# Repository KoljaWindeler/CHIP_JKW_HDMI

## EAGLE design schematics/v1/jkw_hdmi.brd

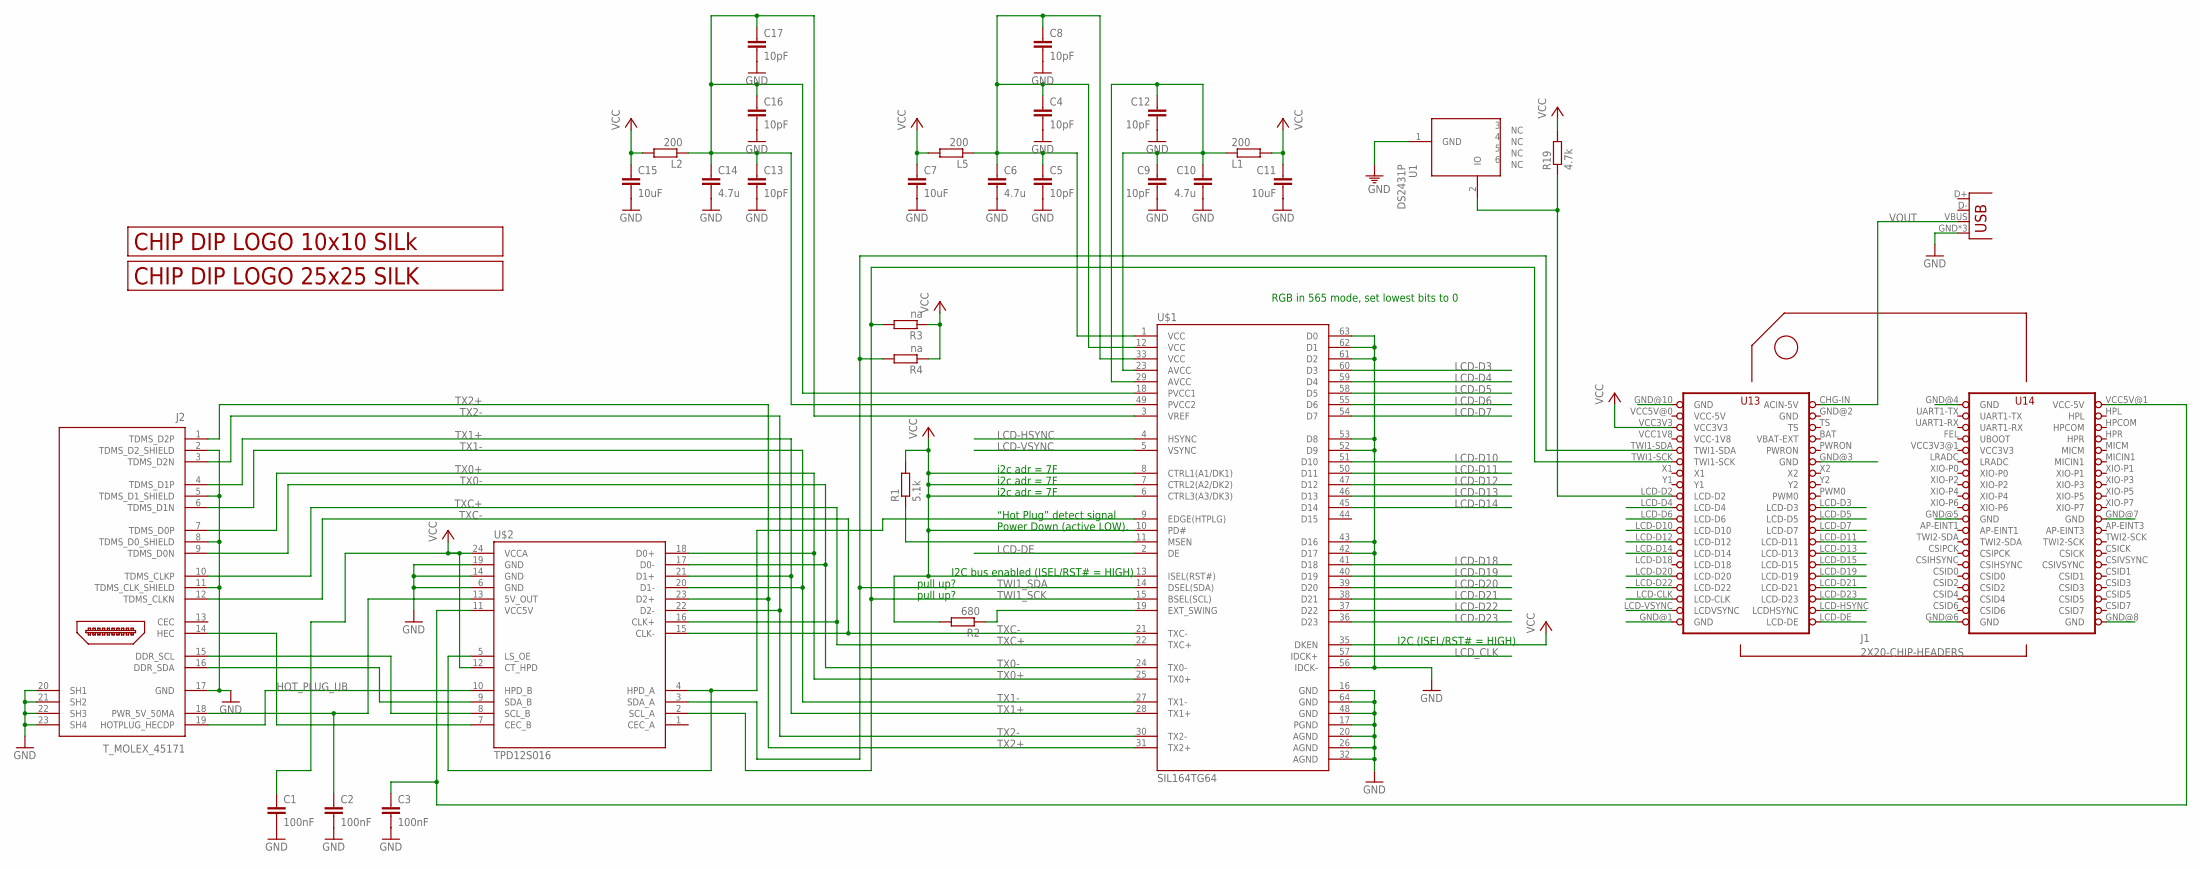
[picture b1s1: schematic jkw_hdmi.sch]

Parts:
C1, C2, C3: 100nF; C0805
C4, C5, C8, C9, C12, C13, C16, C17: 10pF; C0805
C6, C10, C14: 4.7u; C0805
C7, C11, C15: 10uF; C0805
J1: 2X20-CHIP-HEADERS; 2X20CHIP_SM
J2: T_MOLEX_45171
L1, L2, L5: 200; R0805
POWER_USB: USBUSB-MICROB-SMT-DIP; USB-MICROB-SMT-DIP
R1: 5.1k; M0805
R2: 680; M0805
R3, R4: na; M0805
R19: 4.7k; R0805
U1: DS2431P; TSOC6
U$1: SIL164TG64; TQFP64
U$2: TPD12S016; DIL24
U$3: LOGO_10X10_SILK
U$4: LOGO_25X25_SILK

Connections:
ASD: R1.1, U$1.11 (MSEN)
D15: U$1.44 (D15)
GND: C1.2, C2.2, C3.2, C4.2, C5.2, C6.2, C7.2, C8.2, C9.2, C10.2, C11.2, C12.2, C13.2, C14.2, C15.2, C16.2, C17.2, J1.GND@1 (GND), J1.GND@2 (GND), J1.GND@3 (GND), J1.GND@4 (GND), J1.GND@5 (GND), J1.GND@6 (GND), J1.GND@7 (GND), J1.GND@8 (GND), J1.GND@10 (GND), J2.2 (TDMS_D2_SHIELD), J2.5 (TDMS_D1_SHIELD), J2.8 (TDMS_D0_SHIELD), J2.11 (TDMS_CLK_SHIELD), J2.17 (GND), J2.20 (SH1), J2.21 (SH2), J2.22 (SH3), J2.23 (SH4), POWER_USB.GND, POWER_USB.MT1 (GND), POWER_USB.MT2 (GND), U1.1 (GND), U$1.16 (GND), U$1.17 (PGND), U$1.20 (AGND), U$1.26 (AGND), U$1.32 (AGND), U$1.42 (D17), U$1.43 (D16), U$1.48 (GND), U$1.52 (D9), U$1.53 (D8), U$1.56 (IDCK-), U$1.61 (D2), U$1.62 (D1), U$1.63 (D0), U$1.64 (GND), U$2.6 (GND), U$2.14 (GND), U$2.19 (GND)
HOTPLUG_DET: U$1.9 (EDGE(HTPLG)), U$2.4 (HPD_A), U$2.5 (LS_OE)
HOT_PLUG_UB: J2.19 (HOTPLUG_HECDP), U$2.10 (HPD_B)
LCD-D3: J1.LCD-D3, U$1.60 (D3)
LCD-D4: J1.LCD-D4, U$1.59 (D4)
LCD-D5: J1.LCD-D5, U$1.58 (D5)
LCD-D6: J1.LCD-D6, U$1.55 (D6)
LCD-D7: J1.LCD-D7, U$1.54 (D7)
LCD-D10: J1.LCD-D10, U$1.51 (D10)
LCD-D11: J1.LCD-D11, U$1.50 (D11)
LCD-D12: J1.LCD-D12, U$1.47 (D12)
LCD-D13: J1.LCD-D13, U$1.46 (D13)
LCD-D14: J1.LCD-D14, U$1.45 (D14)
LCD-D15: J1.LCD-D15
LCD-D18: U$1.41 (D18)
LCD-D19: J1.LCD-D19, U$1.40 (D19)
LCD-D20: J1.LCD-D20, U$1.39 (D20)
LCD-D21: J1.LCD-D21, U$1.38 (D21)
LCD-D22: J1.LCD-D22, U$1.37 (D22)
LCD-D23: J1.LCD-D23, U$1.36 (D23)
LCD-DE: J1.LCD-DE, U$1.2 (DE)
LCD-HSYNC: J1.LCD-HSYNC (LCDHSYNC), U$1.4 (HSYNC)
LCD-VSYNC: J1.LCD-VSYNC (LCDVSYNC), U$1.5 (VSYNC)
LCD_CLK: J1.LCD-CLK, U$1.57 (IDCK+)
unnamed: R2.1, U$1.19 (EXT_SWING)
unnamed: C2.1, J2.18 (PWR_5V_50MA), U$2.13 (5V_OUT)
unnamed: C4.1, C5.1, C6.1, C8.1, L5.1, U$1.1 (VCC), U$1.12 (VCC), U$1.33 (VCC)
unnamed: J1.LCD-D2, R19.1, U1.2 (IO)
unnamed: J2.15 (DDR_SCL), U$2.8 (SCL_B)
unnamed: J2.16 (DDR_SDA), U$2.9 (SDA_B)
unnamed: C9.1, C10.1, C12.1, L1.1, U$1.23 (AVCC), U$1.29 (AVCC)
unnamed: J2.14 (HEC), U$2.7 (CEC_B)
unnamed: C13.1, C14.1, C16.1, C17.1, L2.1, U$1.3 (VREF), U$1.18 (PVCC1), U$1.49 (PVCC2)
TWI1_SCK: J1.TWI1-SCK, R3.2, U$1.15 (BSEL(SCL)), U$2.2 (SCL_A)
TWI1_SDA: J1.TWI1-SDA, R4.2, U$1.14 (DSEL(SDA)), U$2.3 (SDA_A)
TX0+: J2.7 (TDMS_D0P), U$1.25 (TX0+), U$2.18 (D0+)
TX0-: J2.9 (TDMS_D0N), U$1.24 (TX0-), U$2.17 (D0-)
TX1+: J2.4 (TDMS_D1P), U$1.28 (TX1+), U$2.21 (D1+)
TX1-: J2.6 (TDMS_D1N), U$1.27 (TX1-), U$2.20 (D1-)
TX2+: J2.1 (TDMS_D2P), U$1.31 (TX2+), U$2.23 (D2+)
TX2-: J2.3 (TDMS_D2N), U$1.30 (TX2-), U$2.22 (D2-)
TXC+: J2.10 (TDMS_CLKP), U$1.22 (TXC+), U$2.16 (CLK+)
TXC-: J2.12 (TDMS_CLKN), U$1.21 (TXC-), U$2.15 (CLK-)
VCC: C1.1, C7.1, C11.1, C15.1, J1.VCC3V3, L1.2, L2.2, L5.2, R1.2, R2.2, R3.1, R4.1, R19.2, U$1.6 (CTRL3(A3/DK3)), U$1.7 (CTRL2(A2/DK2)), U$1.8 (CTRL1(A1/DK1)), U$1.10 (PD#), U$1.13 (ISEL(RST#)), U$1.35 (DKEN), U$2.12 (CT_HPD), U$2.24 (VCCA)
VCC3V3: J1.VCC3V3@1 (VCC3V3)
VCC-1V8: J1.VCC1V8 (VCC-1V8)
VCC-5V: J1.VCC5V@0 (VCC-5V)
VCC_5V_DCC: C3.1, J1.VCC5V@1 (VCC-5V), U$2.11 (VCC5V)
VOUT: J1.CHG-IN (ACIN-5V), POWER_USB.VBUS

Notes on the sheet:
I2C bus enabled (ISEL/RST# = HIGH)
RGB in 565 mode, set lowest bits to 0
pull up?
I2C (ISEL/RST# = HIGH)
“Hot Plug” detect signal
Power Down (active LOW).
i2c adr = 7F

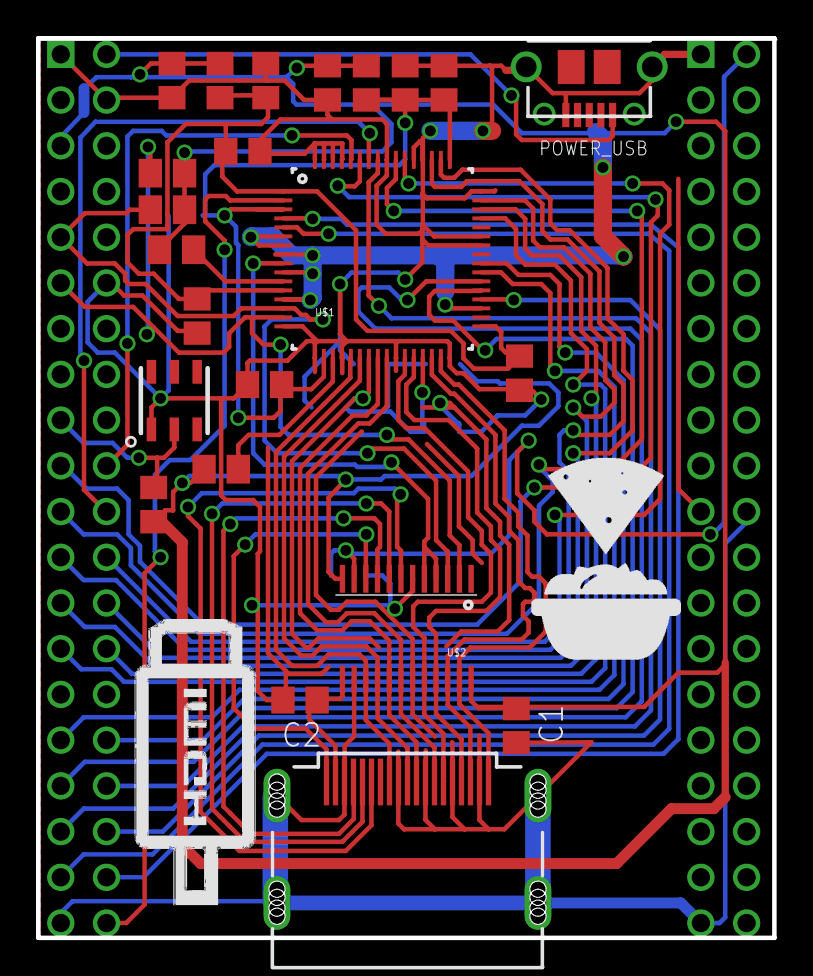
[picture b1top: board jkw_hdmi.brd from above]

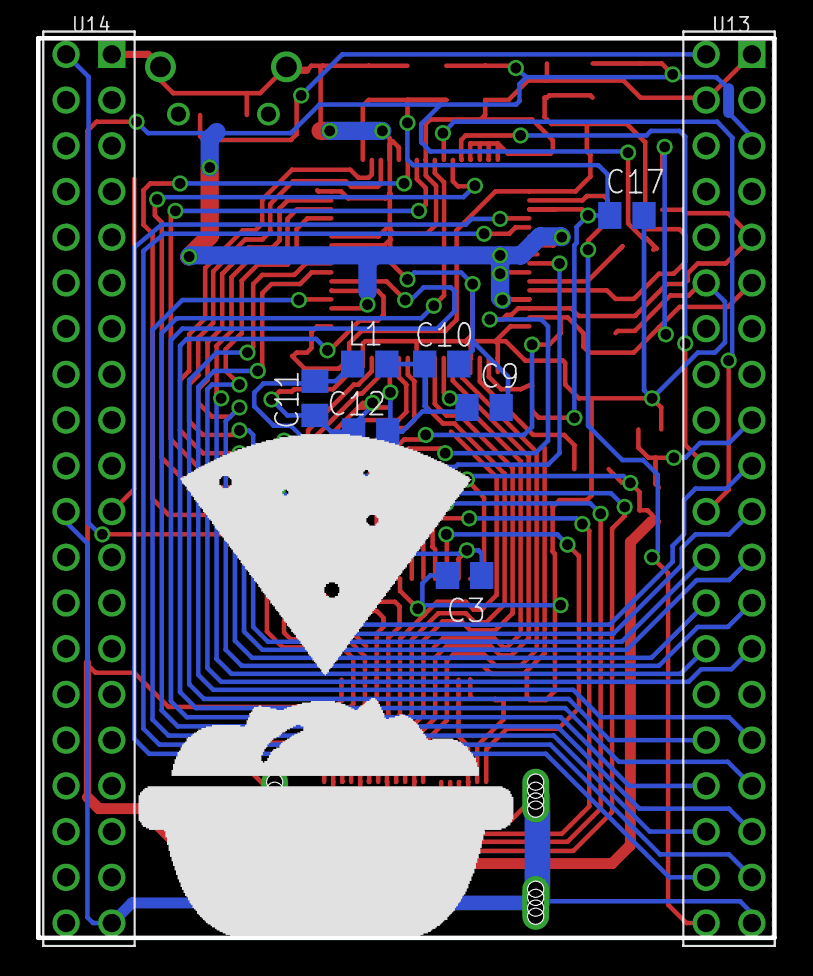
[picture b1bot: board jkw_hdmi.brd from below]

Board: 2 copper layers, 40.9 x 50.0 mm, 33 parts (8 on the bottom side), 45 nets.

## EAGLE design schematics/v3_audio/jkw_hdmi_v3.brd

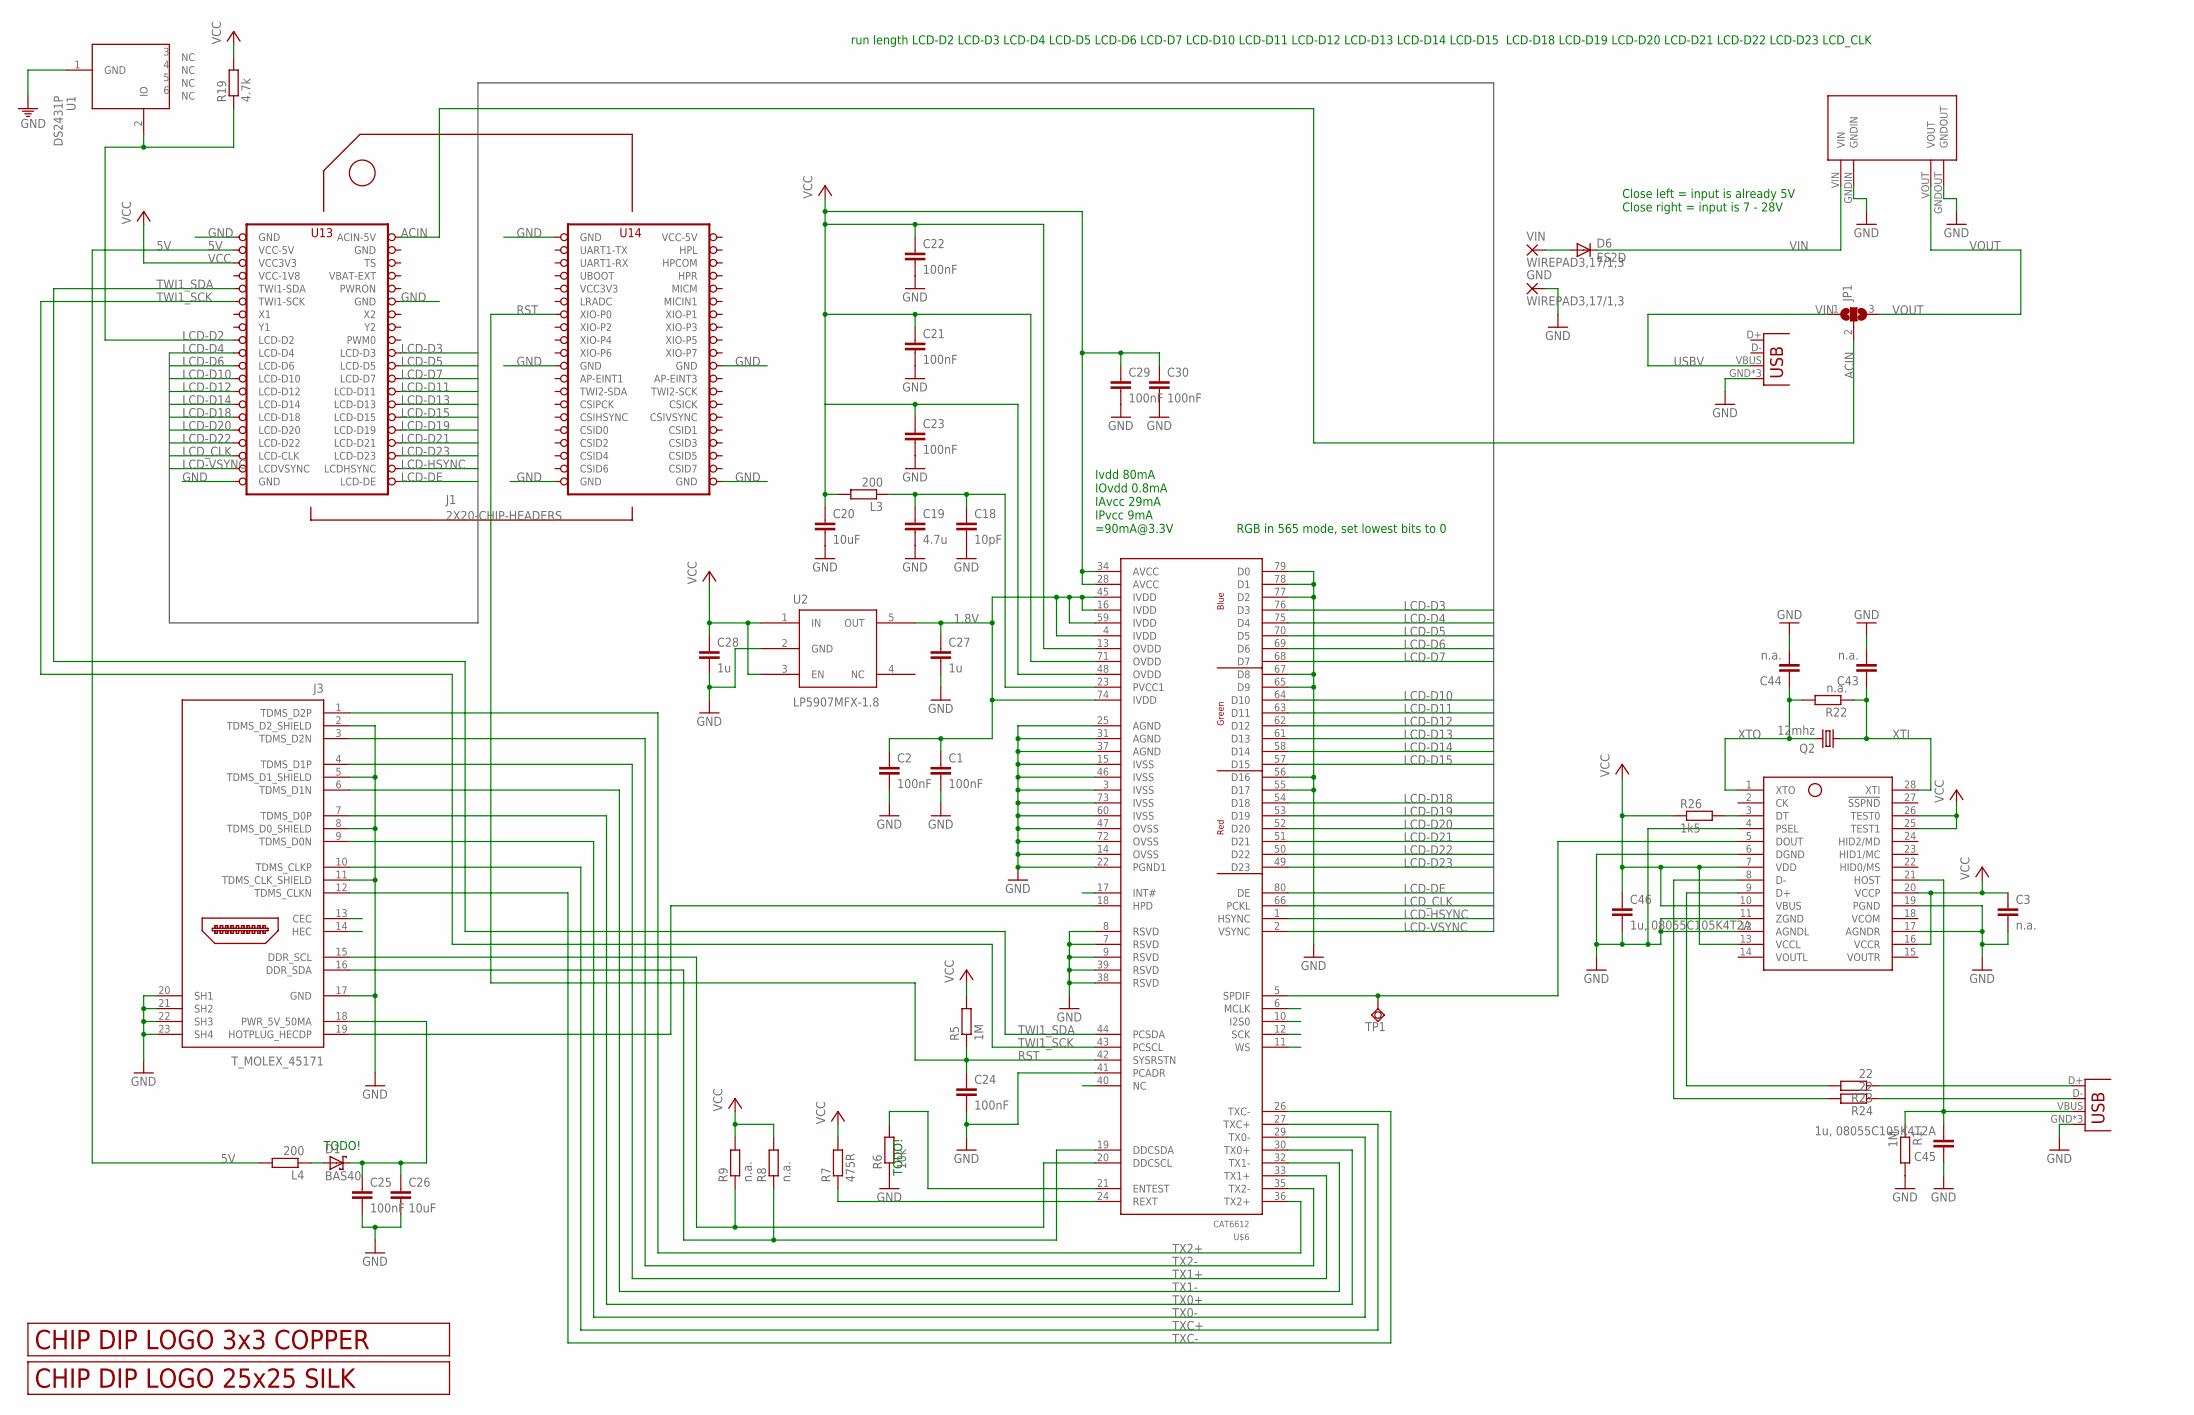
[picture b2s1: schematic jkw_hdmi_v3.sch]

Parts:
AUDIO_USB: USBUSB-MICROB-SMT-DIP; USB-MICROB-SMT-DIP
C1, C2, C21, C22, C23, C24, C25, C29, C30: 100nF; C0805
C3, C43, C44: n.a.; C0805
C18: 10pF; C0805
C19: 4.7u; C0805
C20, C26: 10uF; C0805
C27, C28: 1u; C0805
C45, C46: 1u, 08055C105K4T2A; C0805
D1: BAS40; SOT23
D6: ES2D; SMB
GND: WIREPAD3,17/1,3; 3,17/1,3
J1: 2X20-CHIP-HEADERS; 2X20CHIP_SM
J3: T_MOLEX_45171
JP1: SJ2W; SJ_2
L3, L4: 200; R0805
POWER_USB: USBUSB-MICROB-SMT-DIP; USB-MICROB-SMT-DIP
Q2: 12mhz; HC49UP
R1: 1M; M0805
R5: 1M; R0805
R6: 10k; R0805
R7: 475R; R0805
R8, R9: n.a.; R0805
R19: 4.7k; R0805
R22: n.a.; M0805
R23, R24: 22; M0805
R26: 1k5; M0805
TP1: TPSQTP12SQ; TP12SQ
U1: DS2431P; TSOC6
U2: LP5907MFX-1.8; SOT23-5
U$1: LOGO_25X25_SILK
U$4: LOGO_3X3_COPPER
U$5: PCM2704; SSOT28
U$6: CAT6612; LQFP-80
U$9: MP1584EN_FRAMELESS
VIN: WIREPAD3,17/1,3; 3,17/1,3

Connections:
1.8V: C1.1, C2.1, C27.1, U2.5 (OUT), U$6.4 (IVDD), U$6.16 (IVDD), U$6.45 (IVDD), U$6.59 (IVDD), U$6.74 (IVDD)
5V: J1.VCC5V@0 (VCC-5V), L4.2
ACIN: J1.CHG-IN (ACIN-5V), JP1.2
GND: AUDIO_USB.GND, AUDIO_USB.MT1 (GND), AUDIO_USB.MT2 (GND), C1.2, C2.2, C3.2, C18.2, C19.2, C20.2, C21.2, C22.2, C23.2, C24.2, C25.2, C26.2, C27.2, C28.2, C29.2, C30.2, C43.2, C44.2, C45.1, C46.2, GND.1, J1.GND@1 (GND), J1.GND@2 (GND), J1.GND@3 (GND), J1.GND@4 (GND), J1.GND@5 (GND), J1.GND@6 (GND), J1.GND@7 (GND), J1.GND@8 (GND), J1.GND@10 (GND), J3.2 (TDMS_D2_SHIELD), J3.5 (TDMS_D1_SHIELD), J3.8 (TDMS_D0_SHIELD), J3.11 (TDMS_CLK_SHIELD), J3.17 (GND), J3.20 (SH1), J3.21 (SH2), J3.22 (SH3), J3.23 (SH4), POWER_USB.GND, POWER_USB.MT1 (GND), POWER_USB.MT2 (GND), R1.2, R6.1, U1.1 (GND), U2.2 (GND), U$5.4 (PSEL), U$5.6 (DGND), U$5.11 (ZGND), U$5.12 (AGNDL), U$5.17 (AGNDR), U$5.19 (PGND), U$6.3 (IVSS), U$6.7 (RSVD), U$6.8 (RSVD), U$6.9 (RSVD), U$6.14 (OVSS), U$6.15 (IVSS), U$6.22 (PGND1), U$6.25 (AGND), U$6.31 (AGND), U$6.37 (AGND), U$6.38 (RSVD), U$6.39 (RSVD), U$6.41 (PCADR), U$6.46 (IVSS), U$6.47 (OVSS), U$6.55 (D17), U$6.56 (D16), U$6.60 (IVSS), U$6.65 (D9), U$6.67 (D8), U$6.72 (OVSS), U$6.73 (IVSS), U$6.77 (D2), U$6.78 (D1), U$6.79 (D0), U$9.GNDIN, U$9.GNDOUT
LCD-D2: J1.LCD-D2, R19.1, U1.2 (IO)
LCD-D3: J1.LCD-D3, U$6.76 (D3)
LCD-D4: J1.LCD-D4, U$6.75 (D4)
LCD-D5: J1.LCD-D5, U$6.70 (D5)
LCD-D6: J1.LCD-D6, U$6.69 (D6)
LCD-D7: J1.LCD-D7, U$6.68 (D7)
LCD-D10: J1.LCD-D10, U$6.64 (D10)
LCD-D11: J1.LCD-D11, U$6.63 (D11)
LCD-D12: J1.LCD-D12, U$6.62 (D12)
LCD-D13: J1.LCD-D13, U$6.61 (D13)
LCD-D14: J1.LCD-D14, U$6.58 (D14)
LCD-D15: J1.LCD-D15, U$6.57 (D15)
LCD-D18: J1.LCD-D18, U$6.54 (D18)
LCD-D19: J1.LCD-D19, U$6.53 (D19)
LCD-D20: J1.LCD-D20, U$6.52 (D20)
LCD-D21: J1.LCD-D21, U$6.51 (D21)
LCD-D22: J1.LCD-D22, U$6.50 (D22)
LCD-D23: J1.LCD-D23, U$6.49 (D23)
LCD-DE: J1.LCD-DE, U$6.80 (DE)
LCD-HSYNC: J1.LCD-HSYNC (LCDHSYNC), U$6.1 (HSYNC)
LCD-VSYNC: J1.LCD-VSYNC (LCDVSYNC), U$6.2 (VSYNC)
LCD_CLK: J1.LCD-CLK, U$6.66 (PCKL)
unnamed: J3.19 (HOTPLUG_HECDP), U$6.18 (HPD)
unnamed: C18.1, C19.1, L3.1, U$6.23 (PVCC1)
unnamed: J3.16 (DDR_SDA), R8.1, U$6.19 (DDCSDA)
unnamed: J3.15 (DDR_SCL), R9.1, U$6.20 (DDCSCL)
unnamed: R6.2, U$6.21 (ENTEST)
unnamed: R7.1, U$6.24 (REXT)
unnamed: TP1.TP, U$5.5 (DOUT), U$6.5 (SPDIF)
unnamed: D1.1 (A), L4.1
unnamed: C25.1, C26.1, D1.3 (C), J3.18 (PWR_5V_50MA)
unnamed: R23.2, U$5.9 (D+)
unnamed: AUDIO_USB.D+, R23.1
unnamed: R24.2, U$5.8 (D-)
unnamed: AUDIO_USB.D-, R24.1
unnamed: D6.A, VIN.1
unnamed: R26.2, U$5.3 (DT)
RST: C24.1, J1.XIO-P0, R5.1, U$6.42 (SYSRSTN)
TWI1_SCK: J1.TWI1-SCK, U$6.43 (PCSCL)
TWI1_SDA: J1.TWI1-SDA, U$6.44 (PCSDA)
TX0+: J3.7 (TDMS_D0P), U$6.30 (TX0+)
TX0-: J3.9 (TDMS_D0N), U$6.29 (TX0-)
TX1+: J3.4 (TDMS_D1P), U$6.33 (TX1+)
TX1-: J3.6 (TDMS_D1N), U$6.32 (TX1-)
TX2+: J3.1 (TDMS_D2P), U$6.36 (TX2+)
TX2-: J3.3 (TDMS_D2N), U$6.35 (TX2-)
TXC+: J3.10 (TDMS_CLKP), U$6.27 (TXC+)
TXC-: J3.12 (TDMS_CLKN), U$6.26 (TXC-)
USBV: JP1.1, POWER_USB.VBUS
VCC: C3.1, C20.1, C21.1, C22.1, C23.1, C28.1, C29.1, C30.1, C46.1, J1.VCC3V3, L3.2, R5.2, R7.2, R8.2, R9.2, R19.2, R26.1, U2.1 (IN), U2.3 (EN), U$5.7 (VDD), U$5.10 (VBUS), U$5.13 (VCCL), U$5.16 (VCCR), U$5.20 (VCCP), U$5.25 (TEST1), U$5.26 (TEST0), U$6.13 (OVDD), U$6.28 (AVCC), U$6.34 (AVCC), U$6.48 (OVDD), U$6.71 (OVDD)
VCC2: AUDIO_USB.VBUS, C45.2, R1.1, U$5.21 (HOST)
VCC3V3: J1.VCC3V3@1 (VCC3V3)
VCC-1V8: J1.VCC1V8 (VCC-1V8)
VCC-5V: J1.VCC5V@1 (VCC-5V)
VCOM: U$5.18 (VCOM)
VIN: D6.C, U$9.VIN
VOUT: JP1.3, U$9.VOUT
XTI: C43.1, Q2.1, R22.1, U$5.28 (XTI)
XTO: C44.1, Q2.2, R22.2, U$5.1 (XTO)

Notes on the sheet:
Close left = input is already 5V Close right = input is 7 - 28V
RGB in 565 mode, set lowest bits to 0
TODO!
Ivdd 80mA IOvdd 0.8mA IAvcc 29mA IPvcc 9mA =90mA@3.3V
run length LCD-D2 LCD-D3 LCD-D4 LCD-D5 LCD-D6 LCD-D7 LCD-D10 LCD-D11 LCD-D12 LCD-D13 LCD-D14 LCD-D15 LCD-D18 LCD-D19 LCD-D20 LCD-D21 LCD-D22 LCD-D23 LCD_CLK

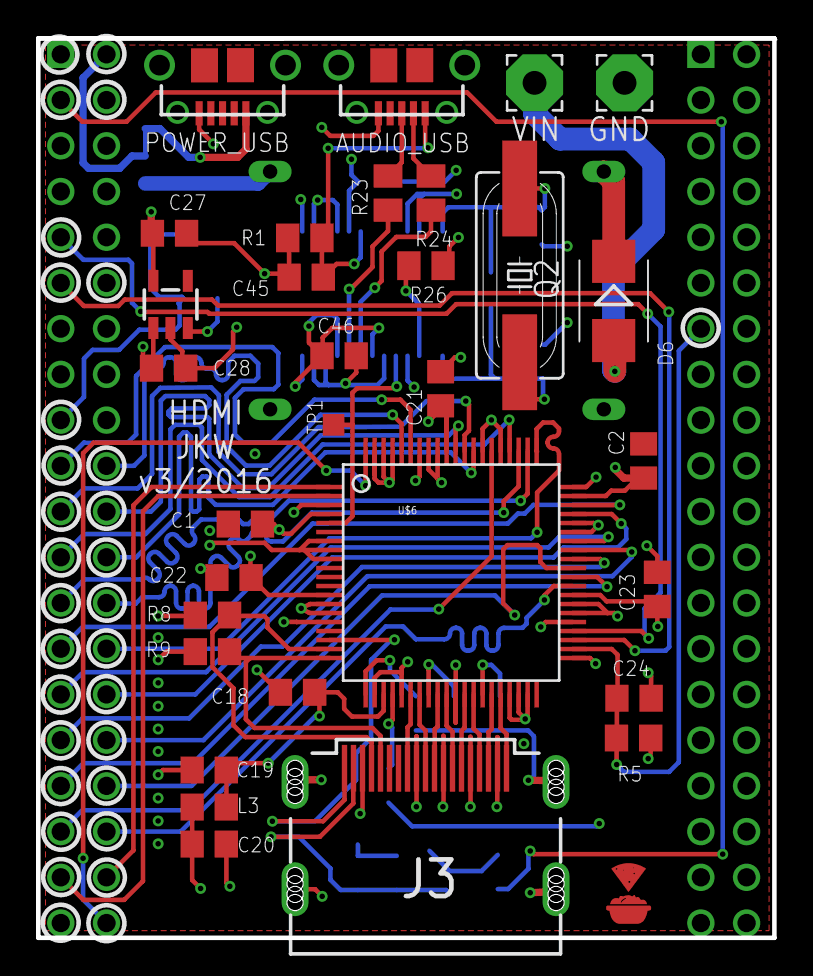
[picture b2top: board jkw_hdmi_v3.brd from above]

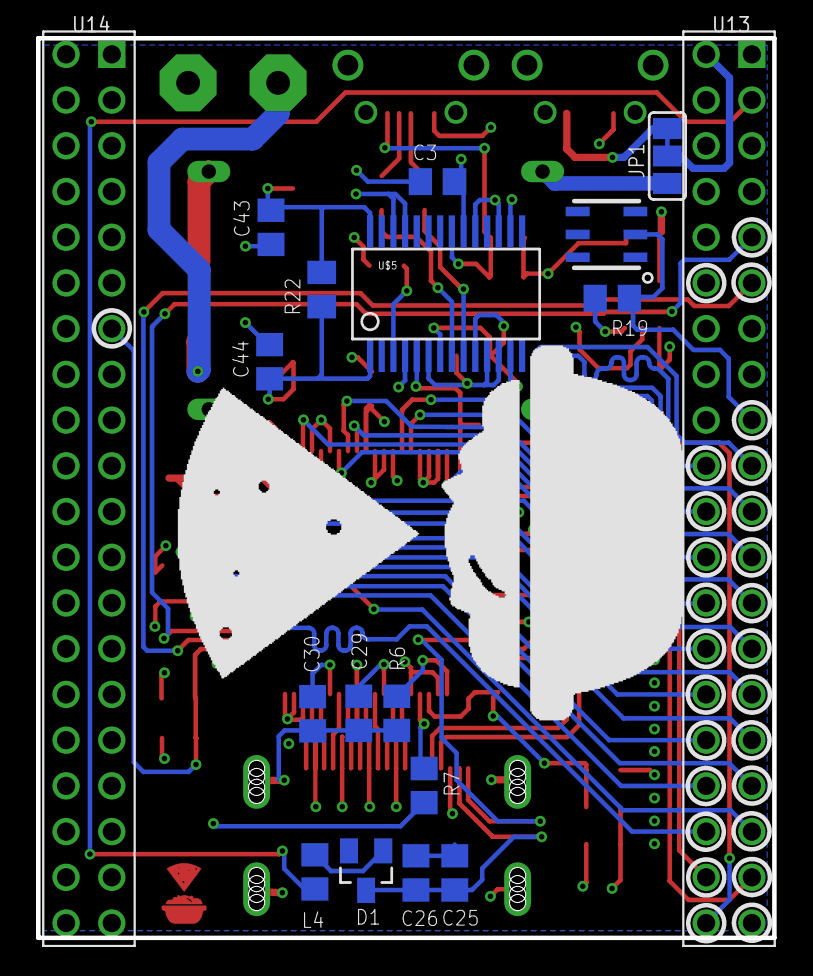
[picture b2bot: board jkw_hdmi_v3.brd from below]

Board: 4 copper layers, 40.9 x 50.0 mm, 51 parts (17 on the bottom side), 59 nets.

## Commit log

2016-07-07 :boom::camel: Added .gitattributes & .gitignore files
2016-07-07 init
2016-07-11 layout 1
2016-07-11 improved silk
2016-07-12 added gerber and ordered design
2016-07-21 added version with minimum drill
2016-07-22 added estimation for quote
2016-07-22 hdmi direct routing
2016-07-22 removed old quotation
2016-07-24 added v2 with DCDC
2016-07-27 new board with audio
2016-07-27 routing v1 done
2016-07-28 removed temp files
2016-07-28 added gitignore for eagle
2016-07-28 updated routing for LCD length matching
2016-07-28 moved zip to subfolder
2016-07-28 moved lib
2016-07-28 added quotation
2016-07-28 added frame
2016-07-28 added solder help
2016-07-28 minor fixes
2016-07-29 gerber v3
2016-08-20 added images
2016-08-31 added programming guide
2016-09-02 added driver code
2016-09-03 added driver v2 code
2016-09-04 next driver version
2016-09-04 Freaking driver works./test !
